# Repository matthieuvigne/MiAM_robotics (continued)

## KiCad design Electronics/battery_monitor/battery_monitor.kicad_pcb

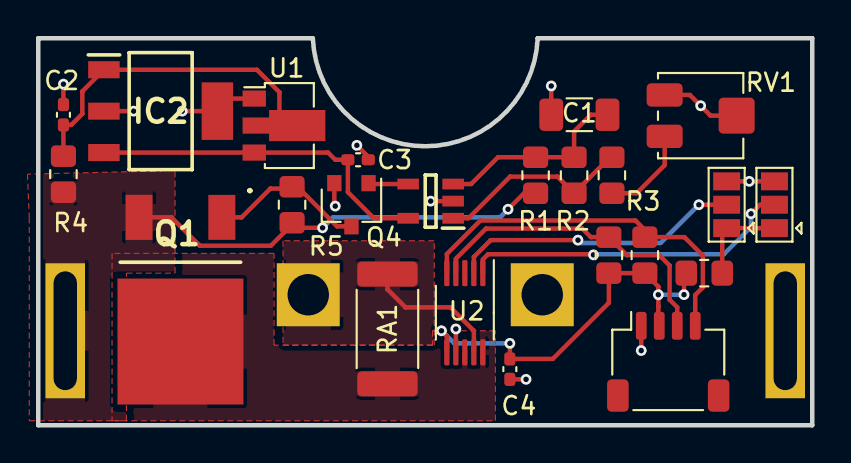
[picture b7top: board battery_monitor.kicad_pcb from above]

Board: 2 copper layers, 43.0 x 21.5 mm, 25 parts (0 on the bottom side), 17 nets.

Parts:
C1: 10uF; C_1206_3216Metric_Pad1.33x1.80mm_HandSolder
C2, C3: 1uF; C_0402_1005Metric_Pad0.74x0.62mm_HandSolder
C4: 0.1uF; C_0402_1005Metric_Pad0.74x0.62mm_HandSolder
IC1: MIC2779H-1YM5_TR; SOT95P280X145-5N
IC2: MCP1790-3302E_DB; SOT230P700X180-4N
J1: Conn_01x04_Male; JST_SH_SM04B-SRSS-TB_1x04-1MP_P1.00mm_Horizontal
J2: Conn_01x02_Pin; BatteryHolder
J3: Conn_01x02_Pin; BatteryHolderOutput
JP1, JP2: SolderJumper_3_Open; SolderJumper-3_P1.3mm_Open_Pad1.0x1.5mm
Q1: DMP4015SK3-13; AZ1084CD50TRG1
Q4: BS170; SC-59
R1: 920k 1%; R_0805_2012Metric_Pad1.20x1.40mm_HandSolder
R2: 5k 1%; R_0805_2012Metric_Pad1.20x1.40mm_HandSolder
R3: 65k; R_0805_2012Metric_Pad1.20x1.40mm_HandSolder
R4: 5; R_0805_2012Metric_Pad1.20x1.40mm_HandSolder
R5: 50k; R_0805_2012Metric_Pad1.20x1.40mm_HandSolder
R6, R7: 4.7k; R_0805_2012Metric_Pad1.20x1.40mm_HandSolder
R8: 75k; R_0805_2012Metric_Pad1.20x1.40mm_HandSolder
RA1: 5mOhm 1% 2W; R_2512_6332Metric_Pad1.40x3.35mm_HandSolder
RV1: 20k; Potentiometer_Bourns_3314J_Vertical
U1: HT7533; LDI8233-05U; SOT-89-3
U2: INA226; VSSOP-10_3x3mm_P0.5mm

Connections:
+3.3V: C4.1, J1.2, R6.1, R7.1, R8.1, U2.6 (VS)
+BATT: J2.1, Q1.3 (S), R1.1, R4.1, R5.1
/A0: JP1.2 (C), U2.2 (A0)
/A1: JP2.2 (C), U2.1 (A1)
/SCL: J1.4, R6.2, U2.5 (SCL)
/SDA: J1.3, R7.2, U2.4 (SDA)
GND: C1.2, C2.1, C3.1, C4.2, IC1.2 (GND), IC2.2 (GND_1), IC2.4 (GND_2), J1.1, J2.2, J3.2, JP1.3 (B), JP2.3 (B), Q4.2 (S), RV1.2, RV1.3, U1.1 (GND), U2.7 (GND)
unnamed: IC1.1 (HTH), R2.2, R3.1
unnamed: C1.1, IC1.3 (LTH), R1.2, R2.1
unnamed: IC1.4 (~RST), Q4.1 (G)
unnamed: C2.2, IC2.1 (VIN), R4.2, U1.2 (VI)
unnamed: J3.1, RA1.1, U2.9 (Vin-)
unnamed: JP1.1 (A), JP2.1 (A), R8.2
unnamed: Q1.1 (G), Q4.3 (D), R5.2
unnamed: R3.2, RV1.1
VCC: Q1.2 (D), RA1.2, U2.8 (Vbus), U2.10 (Vin+)
VDD: C3.2, IC1.5 (VDD), IC2.3 (VOUT), U1.3 (VO)

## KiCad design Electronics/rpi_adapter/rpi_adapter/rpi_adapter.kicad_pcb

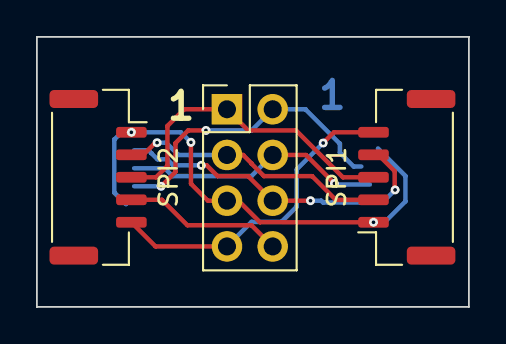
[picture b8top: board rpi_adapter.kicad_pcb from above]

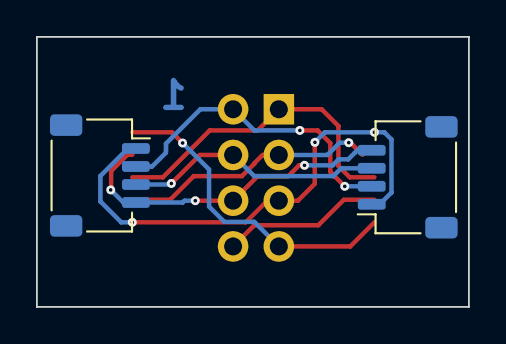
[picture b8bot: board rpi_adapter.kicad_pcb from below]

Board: 2 copper layers, 24.0 x 15.0 mm, 5 parts (2 on the bottom side), 8 nets.

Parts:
J1, J3: Conn_01x04_Male; JST_SH_SM04B-SRSS-TB_1x04-1MP_P1.00mm_Horizontal
J2: Conn_02x05_Odd_Even; PinHeader_2x04_P2.54mm_Vertical
SPI1, SPI2: JST_ZH5; JST_GH_SM05B-GHS-TB_1x05-1MP_P1.25mm_Horizontal

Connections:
+3.3V: J1.2, J2.2, J3.2
/I2C SCL: J1.4, J2.6, J3.4, SPI1.4
/I2C SDA: J1.3, J2.4, J3.3
/SPI MISO: J2.3, SPI1.2, SPI2.2
/SPI MOSI: J2.1, SPI1.3, SPI2.3
/SPI_CS1: J2.8, SPI2.4
GND: J2.7, SPI1.5, SPI2.5
GNDA: J1.1, J2.5, J3.1, SPI1.1, SPI2.1

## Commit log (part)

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2023-05-18 activated flag for primary robot match strategy
2023-05-18 added current checking on servo
2023-05-18 Secondary robot: update score.
2023-05-18 Robot: add panic mode when things go wrong.
2023-05-18 Fixup around motion control.
2023-05-18 Fix replanify SampledTrajectory
2023-05-18 Secondary First match code
2023-05-18 Implement low avoidance zone for secondary
2023-05-18 moved score update for funny action
2023-05-18 corrected end of primary trajectory
2023-05-18 correction2 on Cunegonde
2023-05-18 Add missing file
2023-05-18 Passe vecteur actions en pointeur
2023-05-18 2e match : fix seuils d'évitement et corrige strategie
2023-05-18 Fix goEndPoint for secondary robot
2023-05-18 WIP Implement alternative strat for secondary
2023-05-18 sparse corrections
2023-05-18 Allow exit of panic mode.
    Re-enable rail motion.
2023-05-18 Speed up cherry code
2023-05-18 WIP gui alternate strategy
2023-05-19 Secondary robot: make rail monitoring a standalone thread to avoid creating lag on motion control. Increase RMDX motor timeout. Remove I2C as a required dependency for the code, to remove as much pro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
2023-05-19 slight modifs on primary robot
2023-05-19 GUI: add button to choose strategy (top / bottom start).
2023-05-19 Change cherry actions from testing and disable left distributor
2023-05-19 Refine cherry basket handling and add actions to grab more cherries
2023-05-19 Positions absolues pour distributeurs lateraux
2023-05-21 Add option to rounded corners
2023-05-27 Add motioncontroller drivetrainmotion diagram
2023-05-29 Update diagrams
2023-05-29 BF actions go back to middle
2023-06-15 Fix compilation issues
2023-07-14 Add creating mandatory log dir
2023-07-15 Modify solver weights
2023-07-30 Add breakout board for AS5048B
2023-08-25 Update encoder PCB. Add driver for INA226 power monitor chip.
2023-08-26 [miam_utils] Logger: add text content to logfile.
2023-09-10 Add battery monitor PCB design
2023-10-14 Update code generation for 2024
2023-10-14 Enhance path planning (faster) & add persistent obstacle
2023-10-15 Update final vinyle
2023-10-22 Fix footprint lib path
2023-10-29 Main robot PCB order
2023-11-01 Fix bug in Viewer not starting if waiting for more than MATCH_DURATION. Fix bug in PathPlanner. Cleanup ThreadHandler.
2023-11-17 [code/eurobot2024] Remove secondary robot code ; general cleanup to remove warnings.
2023-11-17 [STSServoDriver] Make class compatible with both STS and SCS servo series.
2023-12-03 Generalize "isStrategyTop" to enable arbitrary start position from a given list
2023-12-10 [main_pcb] Update component footprint for easier soldering
2023-12-16 Add missing GameState file
2023-12-17 Add display of plants being grabbed in simulation
2023-12-19 Enhance traj guess for motion planner
2023-12-23 Implement slowdown based on trajectory anticipation
2024-01-06 Bugfix in NautilusDriver - debug compilation
2024-01-18 Integrate nautilus into robot code.
2024-01-21 Mise a jour des parametres
2024-01-21 [Eurobot2024] Cleanup log names & unused parameters
2024-01-21 Ajout sequence test dans sts_servo_test (changement de mode necessaire)
2024-01-31 [Electronics] Fix main PCB ; add power mosfet PCB
2024-02-13 [miam_py] Fix package structure ; fix miam_analyze_tracking script
2024-02-16 [Strategy] Fix goBackToBase & fix action deadlock
    An action is not retried if it was failed until at least one action has been
    succeeded, or all have failed.
2024-02-17 Fix bug in init phase ; swap right/left motor after hardware change.
2024-02-17 Add point selection & compute trajectory
2024-02-17 "Ajout d'une fonction pour calculer l'angle d'un marker avec la caméra"
2024-02-17 Fix viewer
2024-02-17 BF message sender
2024-02-18 [miam_py] Improve `miam_analyse_tracking`
2024-02-18 Add message type handling
2024-02-18 Fix sending and receiving ids
2024-02-21 Match code: improve servo motion after tests on the robot.
2024-03-02 Add INA226 power monitoring.
2024-03-04 [MPC] Fix bug in trying to enforce endAngle ; minor bugfix to Trapezoid and PathPlanner.
2024-03-11 Add obstacles to MotionController testing. Improve DropPlants action.
2024-03-16 Improve delay in STS code ; misc. changes to main robot strategy.
2024-03-17 Modifs robot viewer
2024-03-30 Update traj planner to new message api
2024-04-06 Strategy: SolarPanels action
2024-04-06 [Strategy] Add action to drop plants into standard zones, using the electromagnets to grab the pots.
    A default strategy is now fully implemented ... in simulation only !
2024-04-06 Add driver for MCP23008 IO expander.
2024-04-06 Add code for electromagnets.
2024-04-06 Script test camera panneaux solaires nouvelle version
2024-04-06 [miam_utils] Rework trajectory API to use enum flag instead of ambiguous list of bool
2024-04-06 corrected get_solar_panel_orientation
2024-04-06 Strategy implementation
2024-04-07 added solar panel camera to vision library and include to main robot code
2024-04-07 miam_py: fix 'latest' option
2024-04-07 Strategy: remove useless turret spin, add final drop action.
2024-04-07 Strategy improvements
2024-04-13 Add fallback mode for encoder in case of reading error.
2024-04-13 Update drivetrain parameters to work correctly in fallback mode.
2024-04-24 Add test for AS5048B encoder
2024-04-27 [miam_utils] Rework logger, replacing HDF5 by custom binary format for performance reasons.
    Logger now logs a custom `.miam` binary format ; use `miam_log_converter` to convert it
    to a more readable HDF5.
2024-04-29 Make SolarPanelCamera asynchronous, and add test code.
2024-05-04 Ajustement positions bras avant suite au rallongement du bras
2024-05-04 Fix symetry of solar panel action. Add debug information about score estimate.
2024-05-04 Add debug information about timing & nautilus driver state.
2024-05-05 Performance improvement to AStar ; integrate it in miam_utils
    Rely on Eigen::Matrix instead of std::vector for walls, giving a significant speedup
    in resolution and printing.
2024-05-05 WIP: drop plants in third pot
2024-05-06 Implement 'panic mode' when an encoder loss of contact is detected.
2024-05-06 ajout offsets pour les panneaux solaires
2024-05-06 Fix bug in encoder loss detection not working on right side.
2024-05-06 Debug code for STS servo driver, running on PC
2024-05-06 Update PathPlanner to rely on static obstacle map.
2024-05-07 Path planning: robot moves back to find an empty cell when starting in obstacle.
    This avoids deadlocks when the other robot is too close.
2024-05-07 Cleanup detection code (remove dead code) ; reduce avoidance timings.
2024-05-07 mise a jour de la strategie, seulement trois panneaux solaires au debut
2024-05-07 Ajout fermeture des pinces pendant le retour
2024-05-07 Lidar: relax number of points and exclusion zone for easier detection.
2024-05-09 Implement debouncing for detection coefficients
2024-05-09 Fix 'out of obstacle' motion to avoid going through the table.
2024-05-09 Minor fixup
2024-05-10 Uncap the limits on velocity for testing
2024-06-10 Implement "unit test" framework to compare pathfinding algorithms
2024-06-14 Tentative implementation of any-angle A* (might be buggy)
2024-10-24 Remove obsolete Astar submodule
2024-10-24 Update rplidar_sdk version to be 64-bits compatible
2024-10-24 Bugfix
2024-12-01 Update PowerSupply PCB
2024-12-02 Update main PCB
2025-01-19 PCB fixup + PCA9546A driver (WIP)
2025-02-22 Add test utility for PCB assembly
2025-02-23 Cleanup eurobot2025 code Add RailServo class
2025-02-23 Test rails on robot
2025-03-15 Complete strategy draft and start testing on the robot
2025-03-15 Fix pullup config on RPi4. Update claw motion of robot
2025-04-13 Rework rail motion through RailManager class
2025-04-18 Add rails to ServoManager
2025-04-19 Update rail translation code
2025-04-19 Tune robot motion parameters
2025-04-20 First match action: try to build first tower
2025-04-21 Prototype action to build level 3 tower Add grid display to MotionController testing
2025-05-08 Add support for tracy profiler
2025-05-08 reimport de libcamera et raspicam sur vision/run_tag_detection
2025-05-08 Rework pathplanning to factor out map manipulation
2025-05-08 Strategy / robot code tweak after testing
2025-05-09 TEST parameters: debugging claws
2025-05-09 test pince dans sts_servo_tests
2025-05-10 STSServoDriver: fix UART timeout issue when using Feetech USB-to-UART converter
2025-05-10 Fixup cmake
2025-05-10 Strategy tweak
2025-05-10 CI fixup
2025-05-10 modifs sur GrabColumnAction
2025-05-10 premier test avec montee trois etages
2025-05-11 ajouts nouveaux essais grabs
2025-05-11 Fixup match end & goBackToBase actions
2025-05-11 Improvement to rplidar tester
2025-05-11 Reduce discontinuity at end of MPC
2025-05-11 Slow down motion for better repeatability
2025-05-25 Adjust robot speed based on claw content
2025-05-25 abaissement a demi niveau des pinces avant grab
2025-05-26 Various tweaks. Add border detection code (disabled for now - not robust)
2025-05-26 Detect other robot and disable other actions based on that.
    Fold robot while moving.
2025-05-26 Fix build action positions
2025-05-27 Fix square avoidance
2025-05-27 Add PAMI exclusion zone
2025-05-27 Add quit button
2025-05-30 Build level 1 tower in case of partial grabs.
2025-05-30 Change grab method and claw motion to try to be more robust to can diameter
2025-05-30 Match 4 modifs
2025-07-05 Rearrange source files in archive/ folder
2025-07-05 Add code for reading BMI088 IMU
2025-07-06 Test sparkfun odometry sensor + IMU + current sensing on robot
2025-12-29 [Elec] V2 of power supply
2025-12-29 Create ServoManager class to improve communication reliability.
2026-01-02 Add main PCB for 2026
2026-01-11 Rework cmake project infrastructure: unify project in a single cmake environment.
2026-02-07 Draw new playmat
2026-02-07 Rename STSServoManager to STSScheduler; add support for rails Cleanup old action code from 2025 Move sts_servo_test to main_robot folder
2026-02-08 Update map obstacles after action
2026-02-08 Add pump to ServoManager
2026-03-28 [TagDetector] Update code to match 2026 camera placement
2026-03-28 [eurobot 2026] Test claw motion. Fix init bug in STSScheduler.
2026-03-29 Add vision to robot
2026-04-17 Add valve code
2026-04-25 Add logging; add gyro bias computation
2026-04-25 Add arm IK
2026-04-25 Add back VLX and cursor action.
2026-04-26 Tweak to CursorAction and servo motions
2026-04-26 Servo action: improve grab
2026-05-09 Tweak to servo actions
2026-05-09 Tweak actions: flip crates
2026-05-10 Border detect: add open-loop mode for finer detection
2026-05-10 Revert border detection to using MotionController
2026-05-10 added beacon detection into rplidar handler
2026-05-10 moved all the beacon detection code back to rpilar handler
2026-05-10 Fix camera focal ; perform visual servoing on robot motion
2026-05-11 Rework robot GUI, add option to prevent startup when arm inside.
2026-05-11 Grab motion: better handling of asym configurations
2026-05-11 Use ESP32 measurements in robot to detect obstacles
2026-05-12 Make gyro optional (disabled by default)
2026-05-12 Tweak arm motion
2026-05-12 Tweak drop action
2026-05-12 VisionHandler: move object to Robot for more robust startup.
2026-05-12 Actions fixup.
2026-05-13 Tweaks
2026-05-14 Avoid loop on release suction.
2026-05-14 Add computation of X offset from camera - but don't use it yet, it doesn't seem to work very well...
2026-05-14 [Match 2 code] Increase robot speed
2026-05-14 Add demo code for grab action.
2026-05-15 [Match 3] Speed up robot motion.
2026-05-15 Update demo
